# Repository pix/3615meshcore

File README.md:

# 3615 MESHCORE

**A [MeshCore](https://github.com/meshcore-dev/MeshCore) LoRa mesh companion whose screen and keyboard are a real French Minitel 2.**

A Seeed XIAO nRF52840 with a Wio-SX1262 sits behind the terminal, wired to its DIN port through a one-transistor interface. On the Minitel you read the mesh, write to it and look after your repeaters, in Télétel style: a service line, inverse title bars, a *Sommaire*, choices typed as a number then **Envoi**. The MeshCore phone app keeps working alongside, with the same identity, contacts and channels.

*The conversation list, rendered from a real `screen` dump of the device by `tools/screenshot/minitel_render.py` (a render, not a photograph).*

Website (in French): **https://pix.github.io/3615meshcore/**, built from `site/`: every screen of the service, features, build guide, reference.

> **En français.** 3615 MESHCORE est un compagnon radio MeshCore dont l'écran et le clavier sont un vrai Minitel 2, piloté par un Seeed XIAO nRF52840 et un Wio-SX1262 branchés sur la prise péri-informatique. Toute la documentation (écrans, fonctions, montage, référence, dépannage) est en français sur le site ; ce README en donne l'essentiel en anglais.

## Features

- **Conversations** on channels, direct messages and rooms, with a history in flash (40 messages × 48 conversations), delivery marks (`(reçu)`, `(échec ?)`), and the hops and SNR of every received message. History back-fill over USB.
- **Dernières nouvelles**: the newest messages of every conversation, merged by time.
- **Contacts**, stations heard on the air, **nearby stations** by distance and bearing, contact sheets with path reset, **trace**, **sharing**, favourites, add-by-key.
- **Rooms and repeater administration**: login, status, neighbours, telemetry, and a **remote console**.
- **Graphs** of SNR, RSSI, noise floor, traffic, airtime against the sub-band duty cycle, battery, best-heard stations, hop counts: Vidéotex G1 mosaics in 40 columns, text plots in 80.
- **French flood regions** named the Gaulix way (`eu > fr > fr-bre > fr-35`), suggested from your position or typed département.
- **Emoji turned into ASCII** (`:-)`, `(y)`, `:pizza:`, `:flag-fr:`); radio text is sanitised so nothing can drive the terminal.
- **Accents typed the Minitel way**: the dead keys, the French set's keys, and `*'e`-style composition.
- A conversation **Actions** page (ENVOI on an empty line): reply, resend, delete a message, message details, search, quick replies, silence, mark all read. Your own channel messages show how many times relays were heard repeating them.
- An **animated welcome page** in four scenes, cheap enough at 9600 baud that a key always enters at once.
- **Both Minitel modes**: Vidéotex 40 columns and Mixte 80 columns.
- **USB command line**: identity backup, clock, history import, **screen dumps**, and **driving the whole UI** from a script.
- **Crash capture** that survives the reset, resolved to a source line from the kept ELF.
- **Standby and répertoire handling**: the node keeps working while the Minitel is off, and sets it up again when it comes back.

## Hardware

| Part | Notes |
|---|---|
| Minitel 2 with the 5-pin DIN "prise péri-informatique" | Developed and tested on a Philips Minitel 2, ROM `Bv9`; other models untested |
| Seeed XIAO nRF52840 + Wio-SX1262 | LoRa on D1–D5, D8–D10 as in MeshCore's `Xiao_nrf52` variant |
| 2N2222A, resistors 10k, 22k, 220k, 9.1k | the interface |
| Male DIN-5 180° plug | |

The interface is **arduiblog's 2N2222A board** from ["Ressuscitez le Minitel"](https://arduiblog.com/2019/04/29/ressuscitez-le-minitel/), powered from the XIAO's **3V3, not 5 V**. It does not invert, so no UART inversion is needed (the nRF52840 cannot invert anyway).

| Interface wire | XIAO |
|---|---|
| the transistor's free outer leg (emitter) | **D6** (Serial1 TX) |
| the wire joined to the 220k and DIN 3, **through a 9.1 kΩ resistor in series** | **D7** (Serial1 RX) |
| supply (220k and 10k) | **3V3** |
| ground (22k and DIN 2) | **GND** |

Minitel DIN pinout, seen from the back of the Minitel (= your plug from its solder side), left to right along the arc: **3 5 2 4 1**.

| DIN pin | Signal | Wire |
|---|---|---|
| 1 | RX, the Minitel's input | transistor collector |
| 2 | GND | XIAO GND |
| 3 | TX, the Minitel's output (open collector) | 220k pull-up to 3V3, then 9.1k to D7 |
| 4 | PT | not connected |
| 5 | +8.5–15 V supply output | **not connected, insulate** |

- If `link log` shows parity errors at 9600 baud, lower the 220k pull-up to about 10k: the weak line picks up glitches from the CRT.
- The Minitel env moves I2C to the NFC pads (`CONFIG_NFCT_PINS_AS_GPIOS`, SDA 30, SCL 31). The first boot writes the UICR, so NFC is gone for good on that XIAO.
- `firmware/minitel-test/` is a stand-alone bring-up sketch for the link alone (`help` on USB). Its README has the verified wiring and test results.
- `hardware/` holds an earlier interface design for a Heltec V3 (KiCad, generated by scripts), kept for reference; the current build is the arduiblog board above.

The build guide on the website (*Montage* page) has the schematic and the DIN drawing.

## Firmware

The firmware and its source are published as a [GitHub release](https://github.com/pix/3615meshcore/releases/latest):

| File | |
|---|---|
| `3615meshcore-xiao_nrf52.uf2` | XIAO nRF52840: double-tap reset, copy it to the USB drive that appears |
| `3615meshcore-xiao_nrf52-dfu.zip` | the same, for serial DFU (`adafruit-nrfutil dfu serial … --touch 1200`) |
| `3615meshcore-firmware-src.tar.gz` | the source: MeshCore's companion radio with the Minitel UI |
| `SHA256SUMS` | checksums |

The UF2 is the application only, for the XIAO's stock bootloader (S140 v7), like any MeshCore XIAO build.

To build it yourself (code in `examples/companion_radio/ui-minitel/`, env `Xiao_nrf52_companion_minitel` in `variants/xiao_nrf52/platformio.ini`, full notes in `docs/companion-minitel.md`):

```sh
tar xzf 3615meshcore-firmware-src.tar.gz
cd 3615meshcore-firmware
pio run -e Xiao_nrf52_companion_minitel -t upload --upload-port /dev/ttyACM0
```

Flashing keeps the file system (identity, contacts, channels, history). If the 1200-baud reset touch misses, retry, or double-tap the XIAO's reset and upload to the bootloader.

First boot: the Minitel starts on its local *répertoire*: leave it with **Fnct + Sommaire**, and disable its automatic standby with **Fnct + E, then A** (**Fnct + E, then M** turns it back on; kept in EEPROM, ROM CV5/BV9 and later). The firmware finds the terminal, switches it to 9600 baud and shows the welcome page. 40/80 columns: RÉPÉTITION on any page, or Réglages 10. The Bluetooth pairing code is drawn at random at each boot and shown on the Minitel when a phone pairs; a fixed one can be set in Réglages 15 (`0` = random again).

### Back up the identity

The node *is* its private key. If the file system is ever erased, it gets a new one. Back it up once over USB:

```
get prv.key          # 128 hex digits: keep them offline
set prv.key <hex>    # restore, then reboot
```

> **Warning.** Anyone with the private key can impersonate the node and read its direct messages. Never paste it into chats, tickets, logs or screenshots.

### USB CLI cheatsheet

USB serial at 115200 baud, CR line ends; replies are indented and end with `OK` or `ERR …`.

| Command | |
|---|---|
| `get prv.key` / `set prv.key <hex>` | identity backup / restore (secret!) |
| `get tz.offset` / `set tz.offset <h>` | time zone, −12 … +14 |
| `clock` / `clock sync <unix>` | read / set the RTC (UTC) |
| `hist list` / `hist add …` / `hist clear <conv>` | history: list, import (never sent), clear |
| `stack`, `boot`, `boot clear` | stack high-water mark and heap; last restart reason and crash record |
| `link log`, `link try <hex>`, `link txlog on\|off\|dump\|clear` | Minitel link diagnostics |
| `ui cursor none\|csi\|cof\|dec`, `redraw` | 80-col cursor hiding; resend the page |
| `screen`, `screen watch <frames> <ms>` | dump the screen model (format v1) |
| `key <name>…`, `type <text>`, `typehex <hex>` | press keys, type text |
| `wait idle [ms]`, `ui state`, `ui reset` | sync with the UI, where it is, back to the Sommaire |
| `splash scene <0-3\|off>`, `splash speed [ms [s]]` | hold a welcome-page scene; its pace |

The full reference, with the dump format, is on the website.

## Host tools

Python 3, run with `python3 -I`. They find the XIAO as `/dev/serial/by-id/*3C0B547619DCA64A*` (edit the serial for yours) and refuse any `/dev/ttyUSB*` device.

| Tool | |
|---|---|
| `tools/screenshot/minitel_dump.py` | fetch a `screen` dump over USB |
| `tools/screenshot/minitel_render.py` | photo-realistic render of a Minitel 2 showing a dump (PNG, GIF, CRT face only); numpy + Pillow. See its README. |
| `tools/tour/tour.py` | walk every page in 40 and 80 columns, save the dumps and `gallery/manifest.json`, record the welcome animation (`screen watch`), rebuild the site. Visits pages only: never sends on the radio. `simulate` tests it offline; `--render` optionally makes photo renders. |
| `site/build.py` | build the website into `site/dist/` (plain files); standard library only |
| `site/tools/make_webfont.py` | rebuild the Minitel web fonts (fontTools, numpy) |

### The website and the gallery

```sh
python3 -I tools/tour/tour.py run --firmware <commit>   # with the XIAO on USB: real captures, then the site
python3 -I site/build.py --check                         # build site/dist/ and check its links
python3 -m http.server -d site/dist     # preview
```

Every screen of the gallery is a real capture from the device, drawn as text by the browser in the Minitel web fonts (mosaics, double size, blink, inverse; selectable and copyable). The only picture on the site is the hero render. The site is static and needs no image renderer.

## Repository layout

```
docs/img/            README pictures
firmware/minitel-test/  bring-up sketch for the link (PlatformIO)
gallery/             real screen dumps + manifest.json
hardware/            earlier Heltec V3 interface (KiCad, generated)
ref/                 protocol notes (third-party manuals are not included)
site/                the website: build.py, content/, templates/, assets/ (fonts, CSS, JS)
tools/screenshot/    dump fetcher, photo renderer, Minitel font
tools/tour/          tour.py
```

## Credits and licences

- **MeshCore** by Scott Powell / rippleradios.com and contributors, MIT.
- **Minitel font**: `Minitel.ttf` / `.sfd` by Frédéric Bisson ([zigazou/minitel-canvas](https://github.com/zigazou/minitel-canvas)), CC0 1.0 (`tools/screenshot/font/LICENSE`). The site's web fonts are rebuilt from it (CC0 as well).
- **Region naming**: [Gaulix, "Règles de nommage des régions et canaux MeshCore"](https://gaulix.fr/docs-parametrage/regles-de-nommage-regions-canaux-meshcore/) and its region generator. Names and geography: INSEE Code officiel géographique 2026 and geo.api.gouv.fr, Licence Ouverte 2.0.
- **Emoji data**: Unicode `emoji-test.txt` (Unicode License v3), github/gemoji (MIT), iamcal/emoji-data (MIT).
- **Interface**: arduiblog, ["Ressuscitez le Minitel"](https://arduiblog.com/2019/04/29/ressuscitez-le-minitel/).
- `firmware/minitel-test/sd_api/` are Nordic Semiconductor SoftDevice headers under their own licence (in each file).
- Not affiliated with Orange, France Télécom, Philips, Seeed Studio or the MeshCore project. "Minitel", "Télétel" and "3615" are used descriptively; no logos.

This repository's own code and documentation: **licence to be chosen** (TODO before publishing).

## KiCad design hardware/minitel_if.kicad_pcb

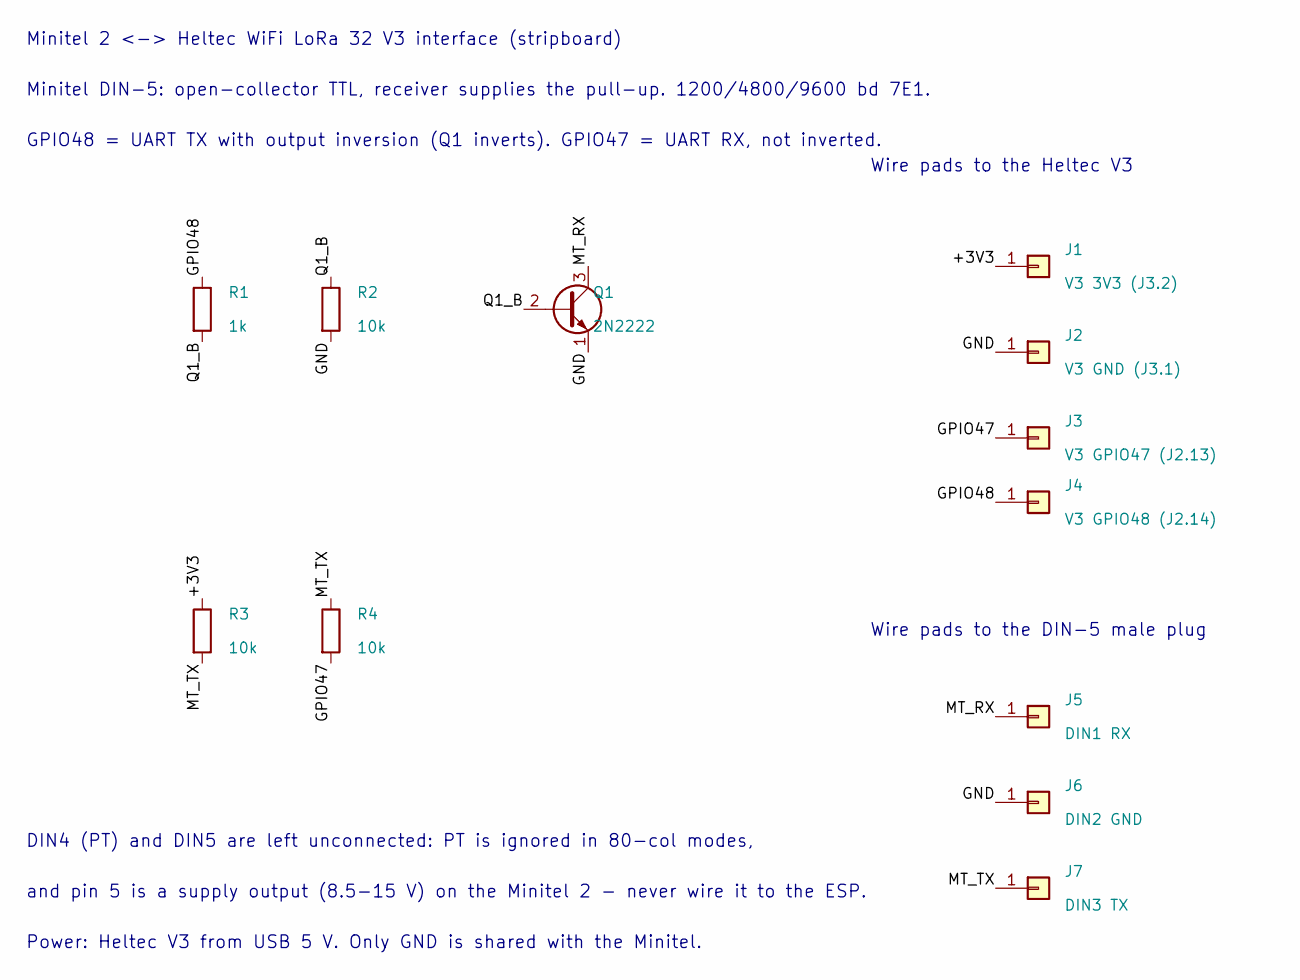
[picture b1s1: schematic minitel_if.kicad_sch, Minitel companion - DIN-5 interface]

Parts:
J1: V3 3V3 (J3.2); WirePad
J2: V3 GND (J3.1); WirePad
J3: V3 GPIO47 (J2.13); WirePad
J4: V3 GPIO48 (J2.14); WirePad
J5: DIN1 RX; WirePad
J6: DIN2 GND; WirePad
J7: DIN3 TX; WirePad
Q1: 2N2222; TO-92_Inline_Wide
R1: 1k; R_Axial_DIN0207_L6.3mm_D2.5mm_P7.62mm_Horizontal
R2, R3: 10k; R_Axial_DIN0207_L6.3mm_D2.5mm_P2.54mm_Vertical
R4: 10k; R_Axial_DIN0207_L6.3mm_D2.5mm_P7.62mm_Horizontal

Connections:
/+3V3: J1.1, R3.1
/GND: J2.1, J6.1, Q1.1 (E), R2.2
/GPIO47: J3.1, R4.2
/GPIO48: J4.1, R1.1
/MT_RX: J5.1, Q1.3 (C)
/MT_TX: J7.1, R3.2, R4.1
/Q1_B: Q1.2 (B), R1.2, R2.1

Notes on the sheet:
Minitel 2 <-> Heltec WiFi LoRa 32 V3 interface (stripboard)
Minitel DIN-5: open-collector TTL, receiver supplies the pull-up. 1200/4800/9600 bd 7E1.
GPIO48 = UART TX with output inversion (Q1 inverts). GPIO47 = UART RX, not inverted.
DIN4 (PT) and DIN5 are left unconnected: PT is ignored in 80-col modes,
and pin 5 is a supply output (8.5-15 V) on the Minitel 2 - never wire it to the ESP.
Power: Heltec V3 from USB 5 V. Only GND is shared with the Minitel.
Wire pads to the Heltec V3
Wire pads to the DIN-5 male plug

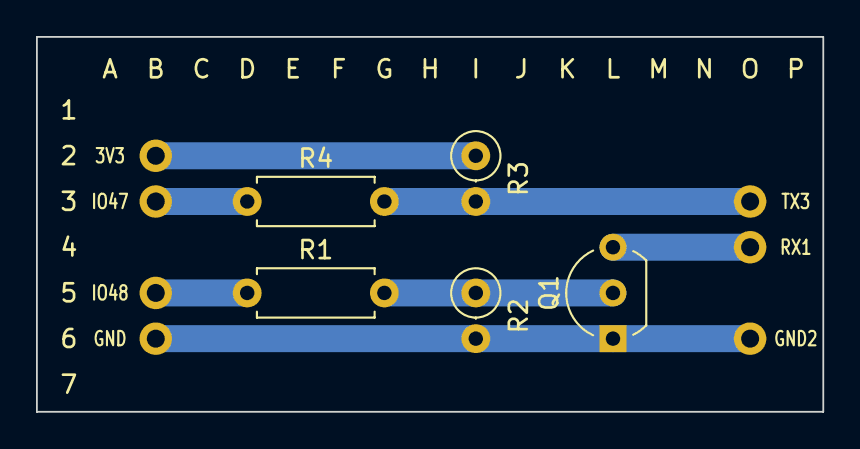
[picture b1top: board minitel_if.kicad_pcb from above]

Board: 2 copper layers, 43.7 x 20.8 mm, 12 parts (0 on the bottom side), 7 nets.
